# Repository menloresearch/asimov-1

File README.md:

# Asimov 1: Open-Source Humanoid Robot

Asimov is an open-source humanoid robot that you can build, train and customize.

<p align="center">
  <a href="https://asimov.inc">Website</a> ·
  <a href="https://manual.asimov.inc">Manual</a> ·
  <a href="https://asimov.inc/diy-kit">DIY Kit</a> ·
  <a href="https://static.asimov.inc/asimov/v1/asimov-v1-20260420.html">3D Model</a> ·
  <a href="https://discord.gg/HzDfGN7kUw">Discord</a> ·
  <a href="https://x.com/asimovinc">X</a> ·
  <a href="https://forum.menlo.ai">Forum</a>
</p>

Asimov 1 is a 1.2 m, 35 kg biped with 25 actuated degrees of freedom. This repository contains the mechanical CAD, electrical CAD, simulation model, and onboard software to build, simulate, and customize Asimov 1.

---

## Specifications

| Spec | Value |
|---|---|
| Height | 1.2 m |
| Weight | 35 kg |
| Degrees of Freedom | 25 actuated |
| Legs | 6 DOF x 2 |
| Arms | 5 DOF x 2 (shoulder pitch/roll/yaw, elbow, wrist yaw) |
| Torso | 1 DOF waist yaw, 10 W 4 ohm speaker, 6 DOF IMU |
| Head | 2 DOF neck (neck yaw, neck pitch), stereo microphone array, 2MP monocular camera |
| CAN Bus | 5 @ 1Mbps + 1 @ 500kbps |
| Onboard Compute | Raspberry Pi 5 (media + network) + Radxa CM5 (motion control) |
| Structural Materials | 7075 aluminium, MJF PA12 nylon |

| Activity | Rated Load | Peak Load |
|---|---|---|
| Squat | 5 kg | - |
| Bicep curl | 5 kg each arm | 15 kg each arm |
| Front raise | 5 kg each arm | 15 kg each arm |
| Lateral raise | 6 kg each arm | 18 kg each arm |

---

## Build your own Asimov

> [!TIP]
> **Option 1: DIY Kit:** Everything you need to build Asimov 1, unassembled. Shipping now for $20,000. [Order now →](https://menlo.ai/asimov-1#buy)

> [!NOTE]
> **Option 2: Self-source:** Pull the [BOM](https://docs.menlo.ai/asimov/1/assembly-preparations/self-source/select-release-and-bom) and fabricate everything yourself. [Assembly Manual →](https://docs.menlo.ai/asimov/1)

### DIY Kit

| Category | Included | Not Included |
|---|---|---|
| Hardware | All BOM components (unassembled), power supply & cabling, spare parts | Tools, hands |
| Compute | RPi edge board, motion control board, network board, power distribution board | 4G/5G modules |
| Sensors | Monocular camera, IMUs, mic, speaker, motor joint states | Lidar, 360 cam |
| Docs | Quick start guide, manual, DIY build videos | — |

**[Pre-order the Asimov 1 DIY Kit →](https://asimov.inc/diy-kit)**

### Self-source

Start with the repo-local [fabrication manifest](mechanical/FABRICATION_MANIFEST.csv) for the CAD-derived part inventory, then cross-reference the [BOM](https://manual.asimov.inc/v1/bom) and assembly manual for procurement details, sourcing, and fabrication notes.

The [shoe accessory](mechanical/accessories/shoes/README.md) is supplied as a single `ASV1_Shoes.STL`. The shoes are symmetric and the same geometry fits either foot: print two identical copies in TPU 95A using FDM, one per foot.

The [dummy hands](mechanical/accessories/dummy_hands/README.md) are supplied as `ASV1_DUMMY_HANDS.3mf`, a Bambu Studio project with embedded printing settings. See the [mechanical fabrication guide](mechanical/README.md) for the part-naming chart and material/process classes, and the [stool accessory](mechanical/accessories/stool/README.md) for its CAD, BOM, and fabrication specifications.

**[Assembly Manual →](https://manual.asimov.inc)**

---

## Fabrication manifest

The fabrication manifest inventories STEP and STL files under `mechanical/ASV1/*/FABRICATION`. Accessories have their own documentation under `mechanical/accessories`. Regenerate the manifest after changing the robot fabrication files, then verify it:

```bash
python3 scripts/generate_fabrication_manifest.py
python3 scripts/generate_fabrication_manifest.py --check
```

---

## Roadmap

| Status | Item |
|---|---|
| ✅ | Mechanical CAD — 7 subassemblies |
| ✅ | MuJoCo simulation model |
| ✅ | Electrical wiring harness |
| ✅ | Electrical schematics & PCB files |
| 🔜 | Asimov Edge |
| 🔜 | Locomotion policy |

---

## Work with us

- **Build questions?**: Ask in the [forum](https://forum.menlo.ai) or open a [GitHub Issue](https://github.com/asimovinc/asimov-v1/issues) for bugs and contributions.
- **Deploying Asimov?**: [Talk to us →](mailto:bd@menlo.ai)
- **Supply chain partner?**: If you manufacture actuators, structural components, or electronics and want to be part of the Asimov supply chain, reach out.
[bd@menlo.ai](mailto:bd@menlo.ai)

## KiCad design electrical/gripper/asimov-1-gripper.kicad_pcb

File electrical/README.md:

## Robot Processing Unit 
### Motion Control Board
- The Motion Control Board (MCB) is a carrier board designed for the Radxa CM5. It has an onboard IMU and contains the necessary motor communication buses for the robot to function.
- The Power Distribution Board (PDB) sits on top of the Motion Control Board (MCB) to form the 2 board stackup.

General information:
- Power is supplied via the XT90(2+2) connector on the PDB, with 5V being routed to the MCB at the bottom
- The UART TTL debug lines have been fanned out as test pads on the PDB for debugging purposes.
- The LSM6DSV IMU is located at the bottom of the MCB
- LCSC component IDs are attached in the KiCad source files for direct JLCPCB fabrication and assembly.

### Communication Ports

| Port Type | Quantity | Details |
|-----------|----------|---------|
| CAN (SPI-CAN) | 6 | CAN via SPI bridge |
| USB 2.0 | 2 | USB interfaces |
| Ethernet | 1 | 1Gbps |
| I2C | 1 | I2C interface |

### Port Mapping

| Port ID | Purpose |
|---------|---------|
| LL | Left leg bus |
| RL | Right leg bus |
| LA | Left arm bus |
| RA | Right arm bus |
| NP | Neck pitch connection for the torso bus |
| NY | Neck yaw connection for the torso bus |
| W  | Waist yaw connection for the torso bus |

> Please refer to the KiCAD source files for a detailed view of all pin mappings on the PDB

## Media Unit

The head of the robot contains a RPI5, with 2 boards to support its function.

Head board:
- contains buck converters to power the RPI5 with 5V
- an audio IC to handle the stereo microphones and stereo speakers, although only 1 speaker output is currently used

RPI5 Hat:
- a small hat that allows for a clean 5V connection to the headers of the RPI5
- contains a button, LED and buzzer for basic status messages, similar to a consumer motherboard

## Wiring

- Each line refers to a pre-made cable on the robot
- Certain connections can only be complete post assembly due to space contraints. These connections have been marked with the Joint names WAGO or SOLDER.

> If making cables from scratch, double-check wire pathing to make sure there is sufficient slack on each connection.

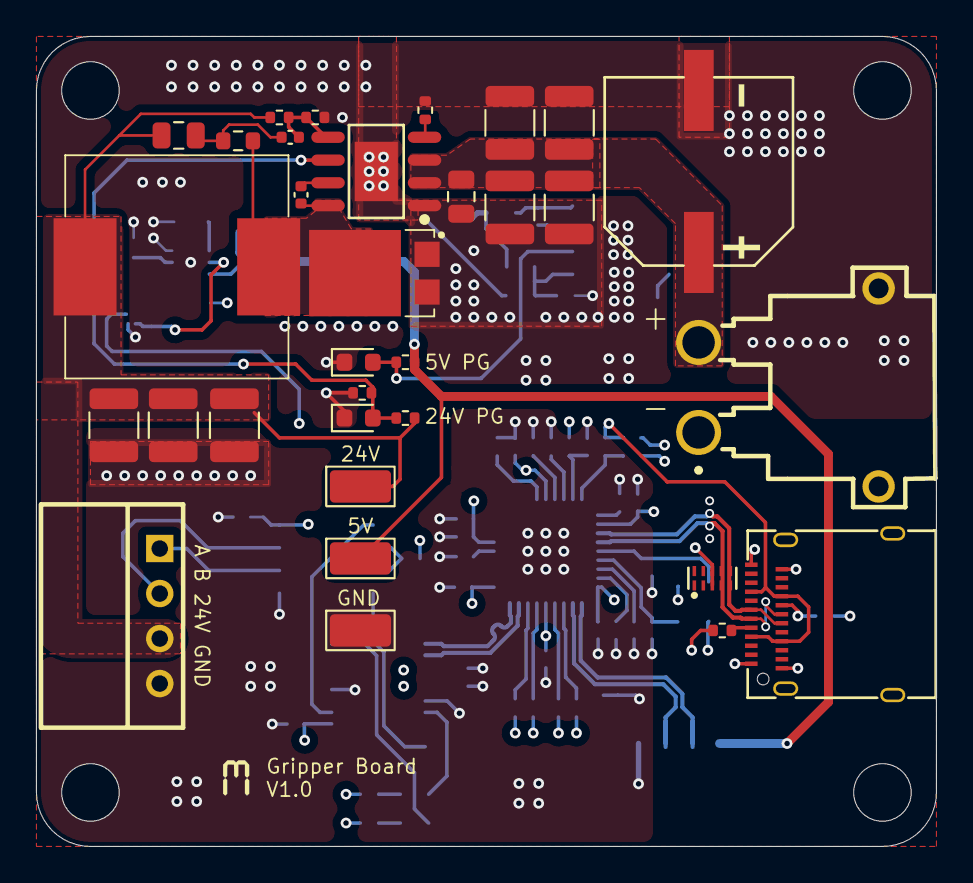
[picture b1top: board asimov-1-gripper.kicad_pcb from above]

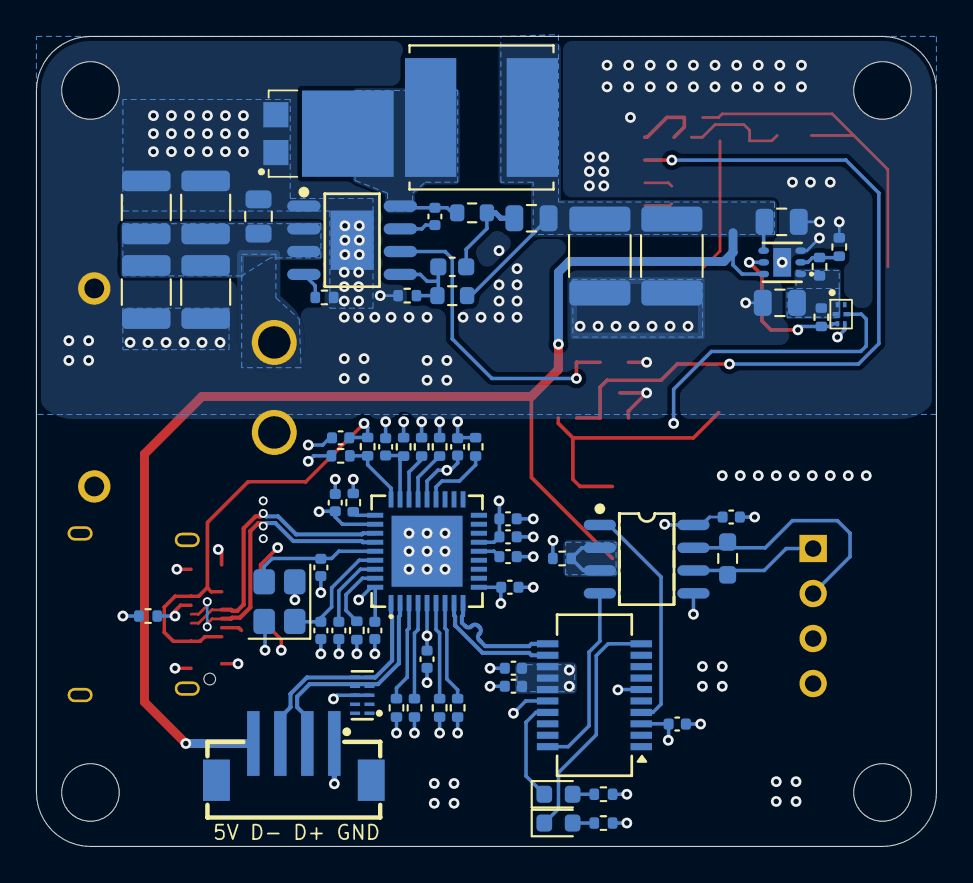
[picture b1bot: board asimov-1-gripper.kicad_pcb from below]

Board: 4 copper layers, 50.0 x 45.0 mm, 102 parts (66 on the bottom side), 53 nets.

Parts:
C101: 100V, 33u; CAP-SMD_BD10.0-L10.3-W10.3-FD
C201, C202, C203, C204, C209, C210, C211, C301, C302, C303, C304: 100V, 10u; C_1210_3225Metric
C205, C305: 100V, 100n; C_0805_2012Metric
C206, C306: 2.2n; C_0402_1005Metric
C207: 47p; C_0402_1005Metric
C208, C308: 3.3n; C_0805_2012Metric
C307: 180p; C_0603_1608Metric
C309, C310: 22u; C_1812_4532Metric
C401, C402: 1u; C_0805_2012Metric
C501, C502, C503, C504, C507, C508, C509, C510, C511, C512, C513, C601, C602, C603, C604: 100n; C_0402_1005Metric
C505, C506: 18p; C_0402_1005Metric
D101, D102: PUSB3FR4Z; DFN2510-10_L2.5-W1.0-P0.50-BL-2
D201, D301, D601, D602: LED_Red; LED_0603_1608Metric
D202, D302: V8P12-M3/86A; TO-277A_L6.1-W4.3-LS6.5-BR
H101, H102, H103, H104: MountingHole; MountingHole_3.2mm_M3
J101: Conn_01x04; CONN-TH_XT30PW-M
J102: USB_C_Receptacle; USB-C-SMD_TYPE-C-24P
J103: Camera USB; CONN-SMD_4P-P1.50_B4B-ZR-SM4-TF
J104: Servo Connection; CONN-TH_22057045
L201: 68u; IND-SMD_L12.0-W12.0_744771008
L301: 47u; IND_SRN8040TA-470M
R101, R102: 5.1k; R_0402_1005Metric
R201: 200k; R_0402_1005Metric
R202, R206, R305: 49.9k; R_0402_1005Metric
R203, R302, R509, R510, R511, R512, R601, R602, R603: 10k; R_0402_1005Metric
R204: 402k; R_0603_1608Metric
R205: 953k; R_0402_1005Metric
R301: 41.2k; R_0402_1005Metric
R303: 180k; R_0603_1608Metric
R304: 158k; R_0603_1608Metric
R401, R403, R501, R502, R503, R504, R505, R506, R507: 100k; R_0402_1005Metric
R402: 20k; R_0402_1005Metric
R508: 12k; R_0402_1005Metric
R604: 120; R_0603_1608Metric_Pad0.98x0.95mm_HandSolder
TP101: GND Test Point; TestPoint_Keystone_5015_Micro_Mini
TP102: 5V Test Point; TestPoint_Keystone_5015_Micro_Mini
TP103: 24V Test Point; TestPoint_Keystone_5015_Micro_Mini
U201, U301: LM5013DDAR; ESOP-8_L4.9-W3.9-P1.27-LS6.0-BL-EP-1
U401: TPS74501PDRVR; WSON-6_L2.0-W2.0-P0.65-TL-EP
U402: TPS22995; DFN-6_L1.3-W0.9_TPS22995RZFR
U501: USB2514BT-I/M2; QFN-36_L6.0-W6.0-P0.50-BL-EP
U601: FT231XS; SSOP-20_3.9x8.7mm_P0.635mm
U602: THVD1406; SOIC-8_L4.9-W3.9-P1.27-LS6.0-BL
Y501: 24MHz 12pF; Crystal_SMD_3225-4Pin_3.2x2.5mm

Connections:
+3V3: C507.1, C508.1, C509.1, C510.1, C511.1, C512.1, C513.1, C601.1, C602.1, C603.1, C604.1, R501.1, R509.1, R510.1, R511.1, R512.1, R601.1, R602.1, R603.2, U402.5 (VOUT), U501.5 (VDDA33), U501.10 (VDDA33), U501.15 (VDD33), U501.23 (VDD33), U501.29 (VDDA33), U501.36 (VDDA33), U601.3 (VCCIO), U601.13 (3V3OUT), U601.14 (~RESET), U601.15 (VCC), U602.8 (VCC)
+5V: C308.2, C309.1, C310.1, C401.1, J103.4, L301.2, R302.1, R304.1, TP102.1 (1_1), U401.4 (EN), U401.6 (IN)
+24V: C208.2, C209.1, C210.1, C211.1, J104.3, L201.2, R202.1, R205.1, TP103.1 (1_1)
+BATT: C101.1, C201.1, C202.1, C203.1, C204.1, C205.1, C301.1, C302.1, C303.1, C304.1, C305.1, J101.2, U201.2 (VIN), U201.3 (EN/UVLO), U301.2 (VIN), U301.3 (EN/UVLO)
/USB2Hub/DFP1_D+: D102.4 (CH3), D102.7 (CH3), J103.2, U501.2 (USBDP_DN1/PRT_DIS_P1)
/USB2Hub/DFP1_D-: D102.5 (CH4), D102.6 (CH4), J103.3, U501.1 (USBDM_DN1/PRT_DIS_M1)
/USB2Hub/DFP4_D+: U501.9 (USBDP_DN4/PRT_DIS_P4), U601.11 (USBDP)
/USB2Hub/DFP4_D-: U501.8 (USBDM_DN4/PRT_DIS_M4), U601.12 (USBDM)
/USB2Hub/UFP_D+: D101.4 (CH3), D101.7 (CH3), J102.A6 (D+), J102.B6 (D+), U501.31 (USBDP_UP)
/USB2Hub/UFP_D-: D101.5 (CH4), D101.6 (CH4), J102.A7 (D-), J102.B7 (D-), U501.30 (USBDM_UP)
/USBToRS485/RS485_A: J104.1, R604.2, U602.6 (A)
/USBToRS485/RS485_B: J104.2, R604.1, U602.7 (B)
/USBToRS485/RX_3V3: U601.4 (RXD), U602.1 (R)
/USBToRS485/TX_3V3: U601.20 (TXD), U602.4 (D)
GND: C101.2, C201.2, C202.2, C203.2, C204.2, C205.2, C209.2, C210.2, C211.2, C301.2, C302.2, C303.2, C304.2, C305.2, C309.2, C310.2, C401.2, C402.2, C501.2, C502.2, C503.2, C504.2, C505.1, C506.1, C507.2, C508.2, C509.2, C510.2, C511.2, C512.2, C513.2, C601.2, C602.2, C603.2, C604.2, D101.3 (GND), D101.8 (GND), D102.3 (GND), D102.8 (GND), D201.1 (K), D202.1 (A), D202.2 (A), D301.1 (K), D302.1 (A), D302.2 (A), J101.1, J101.3, J101.4, J102.A1 (GND), J102.A12 (GND), J102.B1 (GND), J102.B12 (GND), J103.1, J104.4, R101.2, R102.2, R201.2, R203.1, R206.2, R301.2, R305.2, R402.2, R503.2, R504.1, R505.1, R506.1, R507.1, R508.2, TP101.1 (1_1), U201.1 (GND), U201.9 (EP), U301.1 (GND), U301.9 (EP), U401.3 (GND), U401.7 (EP), U402.4 (GND), U501.37 (EP), U601.6 (GND), U601.16 (GND), U602.5 (GND), Y501.2 (G), Y501.4 (G)
unnamed: C207.1, C208.1, R204.2
unnamed: C307.1, C308.1, R303.2
unnamed: D201.2 (A), R202.2, R203.2, U201.6 (PGOOD)
unnamed: C206.2, D202.3 (K), L201.1, R204.1, U201.8 (SW)
unnamed: D301.2 (A), R302.2, U301.6 (PGOOD)
unnamed: C306.2, D302.3 (K), L301.1, R303.1, U301.8 (SW)
unnamed: D601.2 (A), R601.2
unnamed: D601.1 (K), U601.17 (CBUS1)
unnamed: D602.2 (A), R602.2
unnamed: D602.1 (K), U601.10 (CBUS2)
unnamed: J102.A5 (CC1), R101.1
unnamed: J102.B5 (CC2), R102.1
unnamed: C206.1, U201.7 (BST)
unnamed: C207.2, R205.2, R206.1, U201.5 (FB)
unnamed: R201.1, U201.4 (RON)
unnamed: C306.1, U301.7 (BST)
unnamed: C307.2, R304.2, R305.1, U301.5 (FB)
unnamed: R301.1, U301.4 (RON)
unnamed: R401.2, R402.1, U401.2 (FB)
unnamed: C402.1, R401.1, R403.1, U401.1 (OUT), U402.1 (VBIAS), U402.2 (VIN)
unnamed: R403.2, U401.5 (PG), U402.3 (ON)
unnamed: C502.1, U501.14 (CRFILT)
unnamed: R505.2, U501.25 (HS_IND/CFG_SEL1)
unnamed: C504.1, U501.34 (PLLFILT)
unnamed: R508.1, U501.35 (RBIAS)
unnamed: C501.1, R501.2, U501.26 (RESET_N)
unnamed: R504.2, U501.24 (SCL/SMBCLK/CFG_SEL0)
unnamed: R507.2, U501.22 (SDA/SMBBATA/NON_REM1)
unnamed: R506.2, U501.28 (SUSP_IND/LOCAL_PWR/NON_REM0)
unnamed: R509.2, U501.3 (USBDM_DN2/PRT_DIS_M2)
unnamed: R511.2, U501.6 (USBDM_DN3/PRT_DIS_M3)
unnamed: R510.2, U501.4 (USBDP_DN2/PRT_DIS_P2)
unnamed: R512.2, U501.7 (USBDP_DN3/PRT_DIS_P3)
unnamed: R502.2, R503.1, U501.27 (VBUS_DET)
unnamed: C505.2, U501.33 (XTALIN/CLKIN), Y501.1
unnamed: C506.2, U501.32 (XTALOUT), Y501.3
unnamed: R603.1, U602.2 (~RE), U602.3 (~SHDN)
VBUS: C503.1, J102.A4 (VBUS), J102.A9 (VBUS), J102.B4 (VBUS), J102.B9 (VBUS), R502.1

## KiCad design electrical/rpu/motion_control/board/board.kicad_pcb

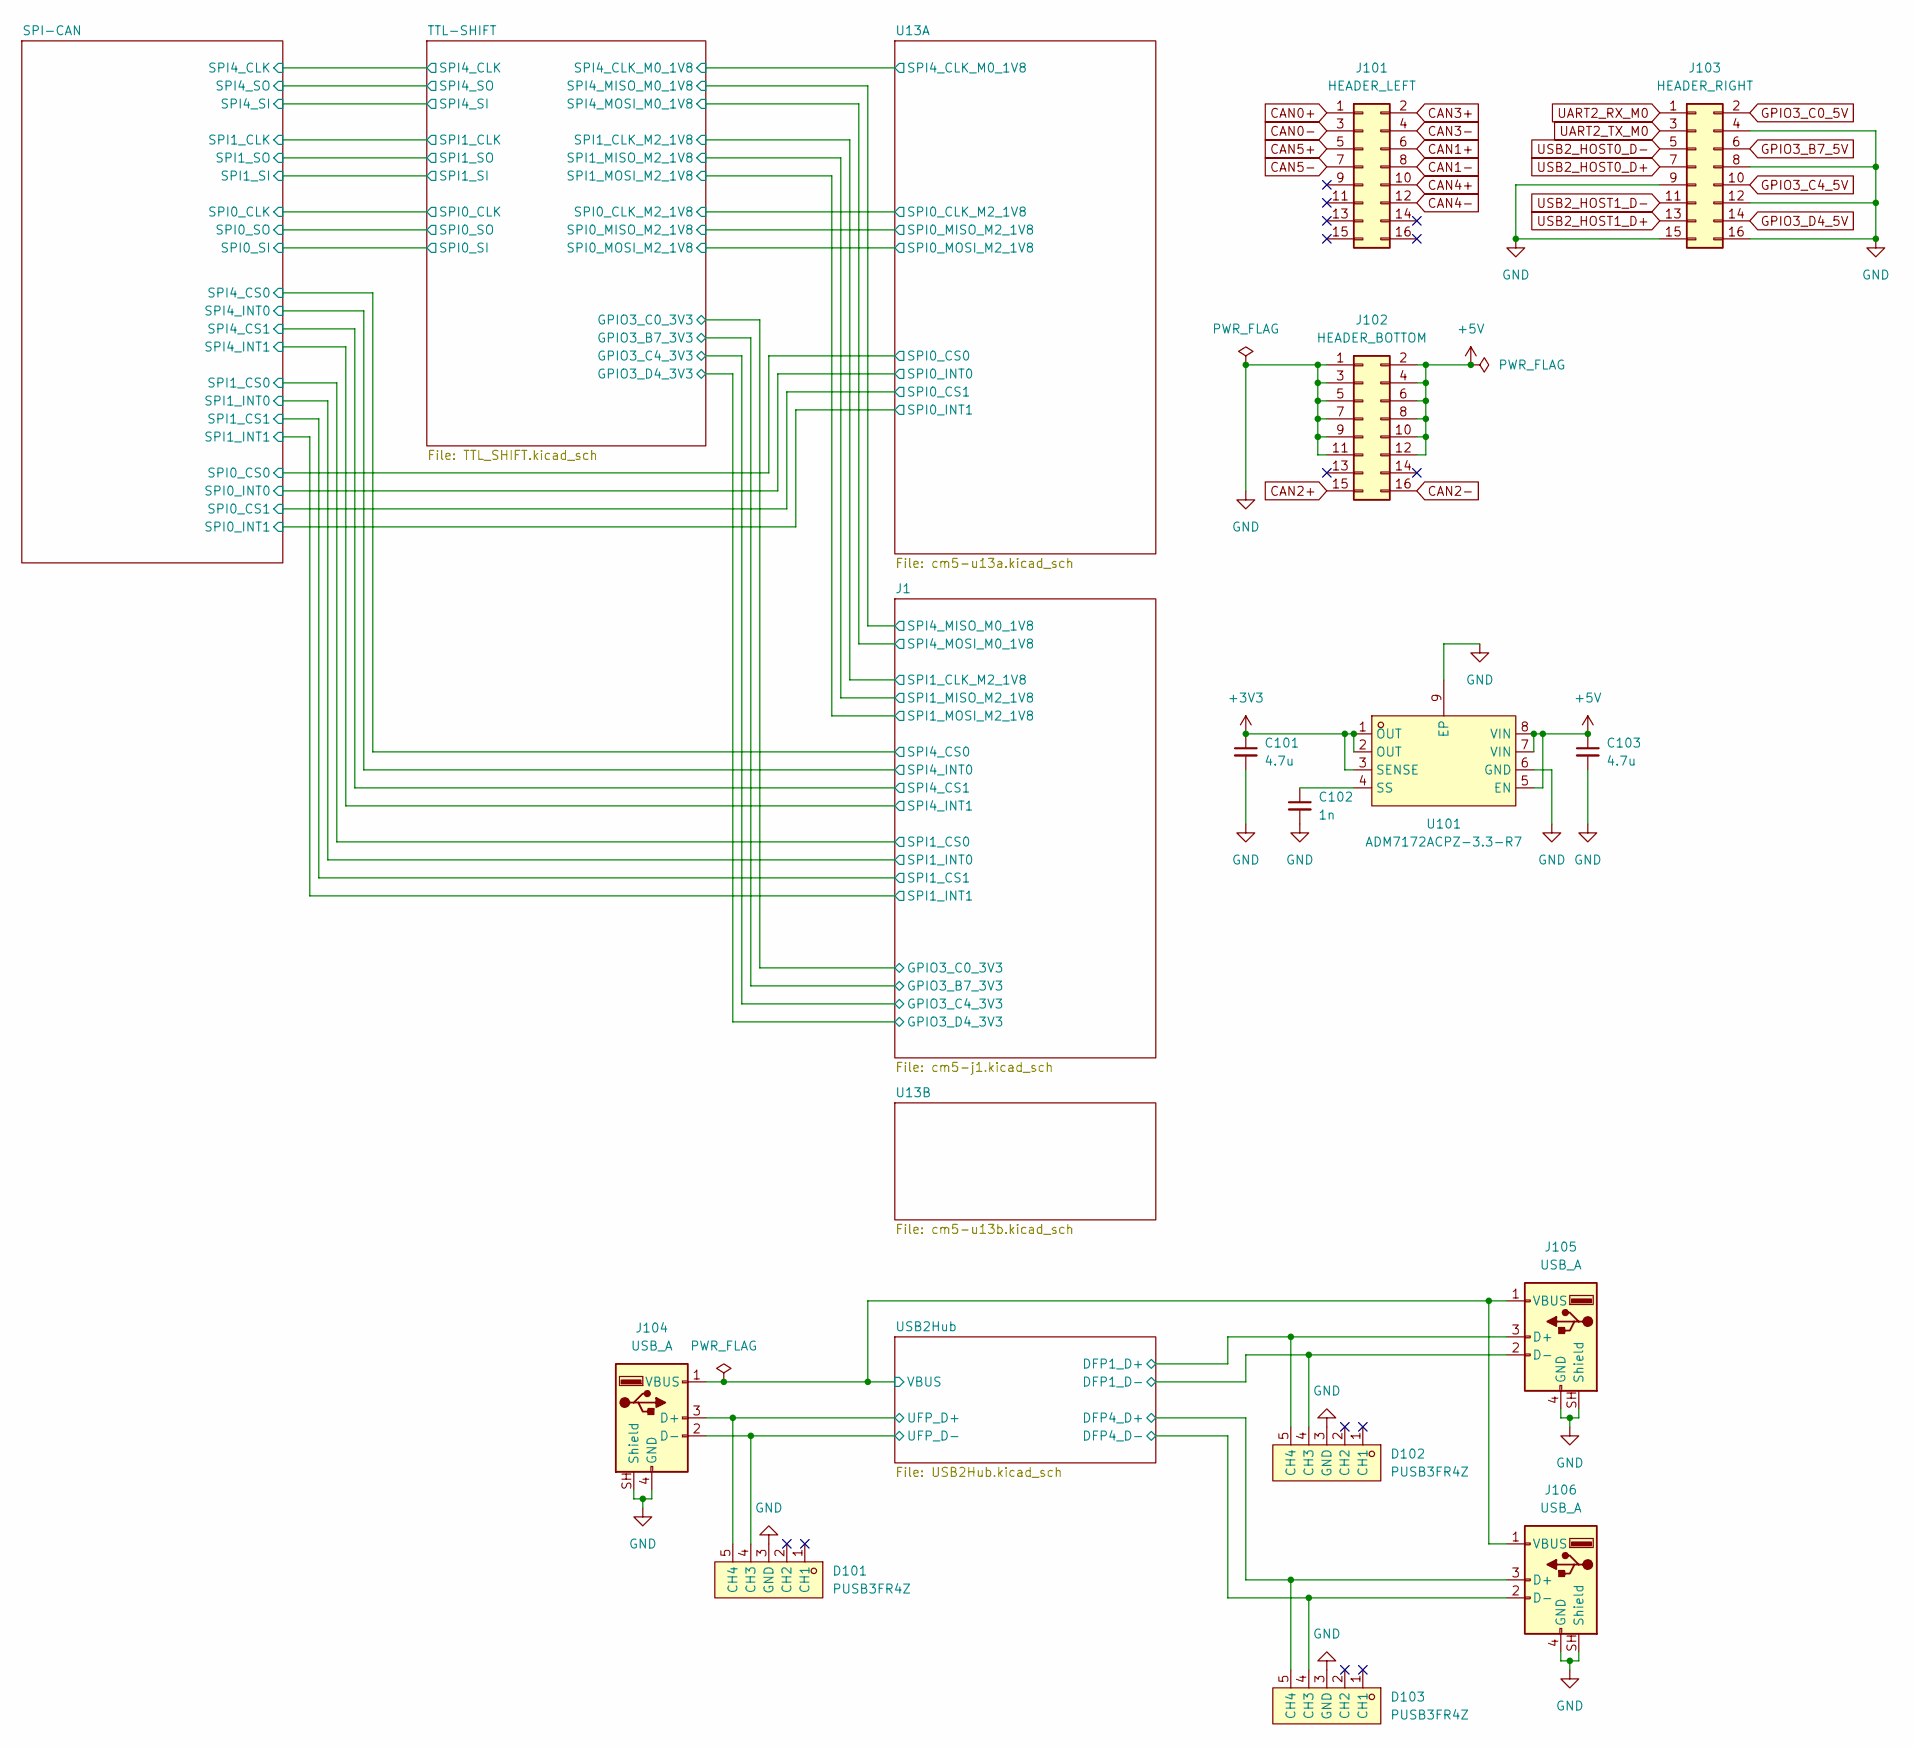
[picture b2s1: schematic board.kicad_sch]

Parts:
C101, C103: 4.7u; C_0402_1005Metric; LCSC C368809
C102: 1n; C_0402_1005Metric; LCSC C76947
D101, D102, D103: PUSB3FR4Z; DFN2510-10_L2.5-W1.0-P0.50-BL-2; MPN PUSB3FR4Z; LCSC Part C503418
J101: HEADER_LEFT; PinHeader_2x08_P2.54mm_Vertical; LCSC C492425
J102: HEADER_BOTTOM; PinHeader_2x08_P2.54mm_Vertical; LCSC C492425
J103: HEADER_RIGHT; PinHeader_2x08_P2.54mm_Vertical; LCSC C492425
J104, J105, J106: USB_A; USB-A-TH_FUS264-FDSW3K; LCSC C305910
U101: ADM7172ACPZ-3.3-R7; DFN-8_L3.0-W3.0-P0.50-BL-EP; MPN ADM7172ACPZ-3.3-R7; LCSC Part C514342

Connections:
+3V3: C101.1, U101.1 (OUT), U101.2 (OUT), U101.3 (SENSE); also elsewhere on the board
+5V: C103.1, J102.2, J102.4, J102.6, J102.8, J102.10, J102.12, U101.5 (EN), U101.7 (VIN), U101.8 (VIN); also elsewhere on the board
/USB2Hub/DFP1_D+: D102.5 (CH4), D102.6 (CH4), J105.3 (D+); also elsewhere on the board
/USB2Hub/DFP1_D-: D102.4 (CH3), D102.7 (CH3), J105.2 (D-); also elsewhere on the board
/USB2Hub/DFP4_D+: D103.5 (CH4), D103.6 (CH4), J106.3 (D+); also elsewhere on the board
/USB2Hub/DFP4_D-: D103.4 (CH3), D103.7 (CH3), J106.2 (D-); also elsewhere on the board
/USB2Hub/UFP_D+: D101.5 (CH4), D101.6 (CH4), J104.3 (D+); also elsewhere on the board
/USB2Hub/UFP_D-: D101.4 (CH3), D101.7 (CH3), J104.2 (D-); also elsewhere on the board
/USB2Hub/VBUS: J104.1 (VBUS), J105.1 (VBUS), J106.1 (VBUS); also elsewhere on the board
CAN0+: J101.1; also elsewhere on the board
CAN0-: J101.3; also elsewhere on the board
CAN1+: J101.6; also elsewhere on the board
CAN1-: J101.8; also elsewhere on the board
CAN2+: J102.15; also elsewhere on the board
CAN2-: J102.16; also elsewhere on the board
CAN3+: J101.2; also elsewhere on the board
CAN3-: J101.4; also elsewhere on the board
CAN4+: J101.10; also elsewhere on the board
CAN4-: J101.12; also elsewhere on the board
CAN5+: J101.5; also elsewhere on the board
CAN5-: J101.7; also elsewhere on the board
GND: C101.2, C102.2, C103.2, D101.3 (GND), D101.8 (GND), D102.3 (GND), D102.8 (GND), D103.3 (GND), D103.8 (GND), J102.1, J102.3, J102.5, J102.7, J102.9, J102.11, J103.4, J103.8, J103.9, J103.12, J103.15, J103.16, J104.4 (GND), J104.SH (Shield), J105.4 (GND), J105.SH (Shield), J106.4 (GND), J106.SH (Shield), U101.6 (GND), U101.9 (EP); also elsewhere on the board
GPIO3_B7_5V: J103.6; also elsewhere on the board
GPIO3_C0_5V: J103.2; also elsewhere on the board
GPIO3_C4_5V: J103.10; also elsewhere on the board
GPIO3_D4_5V: J103.14; also elsewhere on the board
unnamed: C102.1, U101.4 (SS)
UART2_RX_M0: J103.1; also elsewhere on the board
UART2_TX_M0: J103.3; also elsewhere on the board
USB2_HOST0_D+: J103.7; also elsewhere on the board
USB2_HOST0_D-: J103.5; also elsewhere on the board
USB2_HOST1_D+: J103.13; also elsewhere on the board
USB2_HOST1_D-: J103.11; also elsewhere on the board

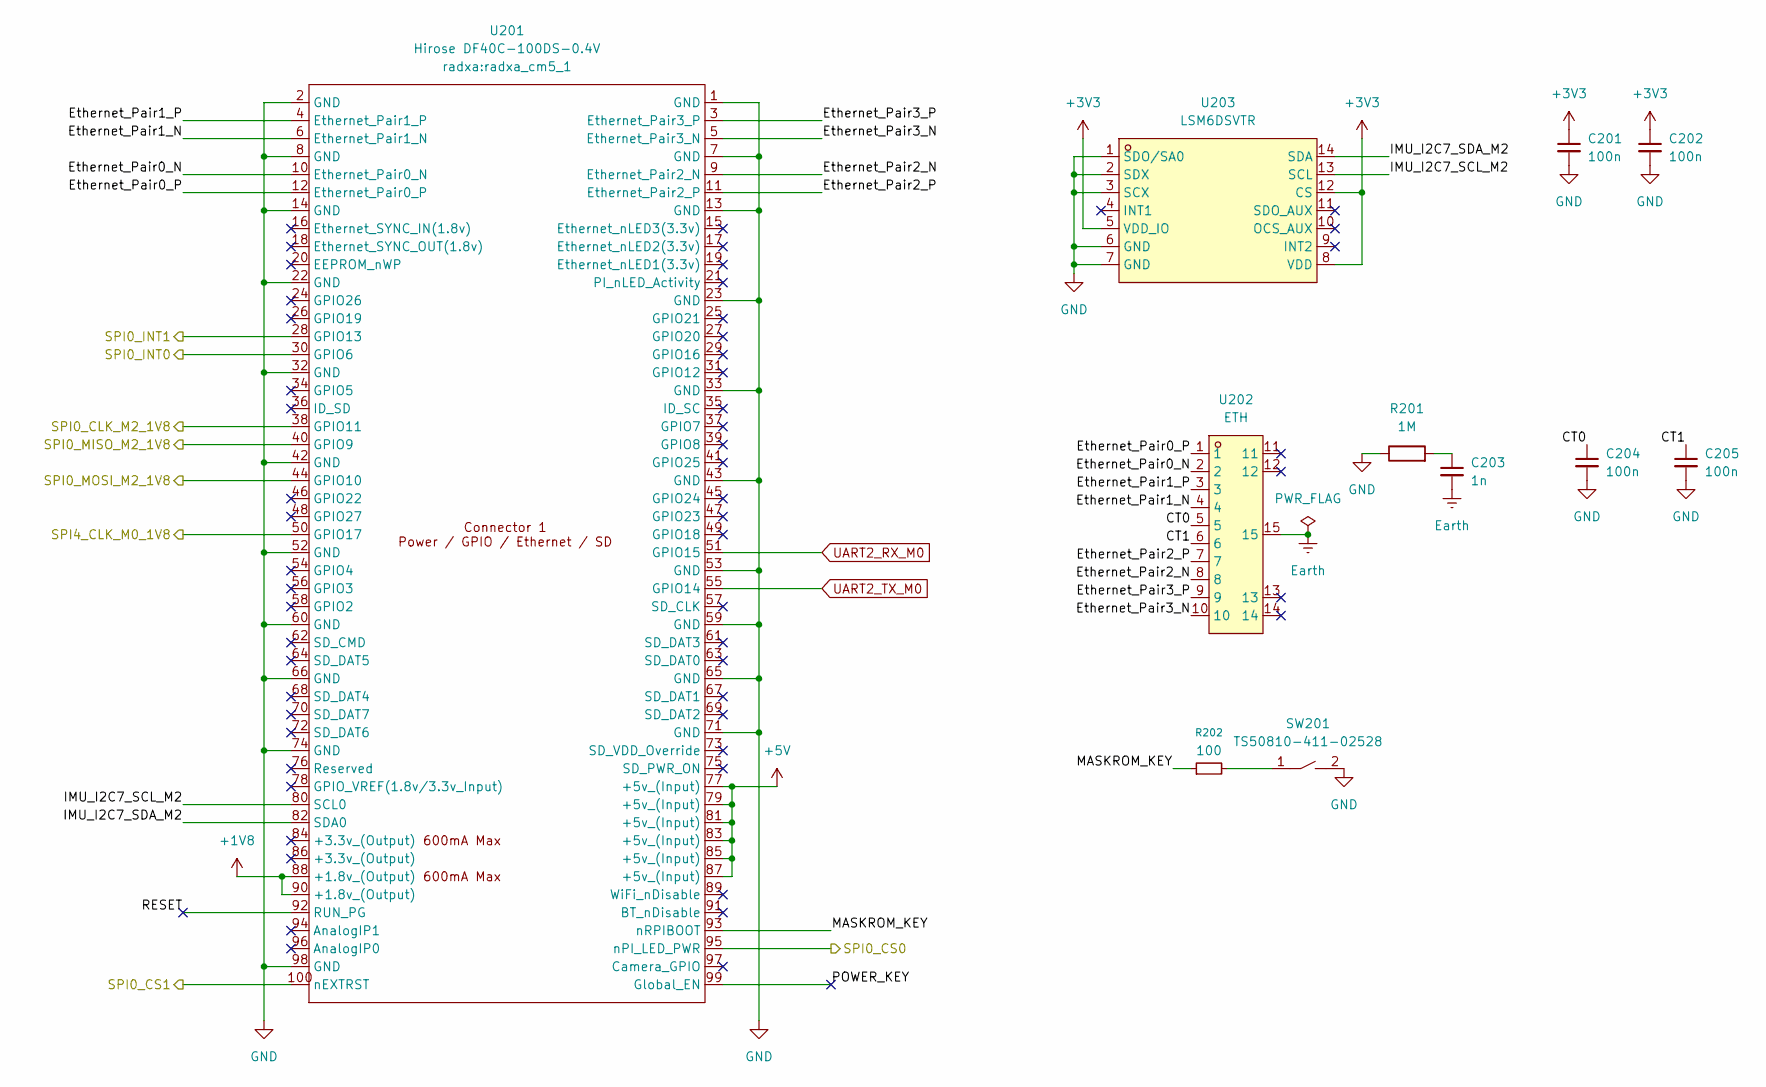
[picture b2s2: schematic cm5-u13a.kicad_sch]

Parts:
C201, C202: 100n; C_0402_1005Metric; LCSC C77020
C203: 1n; C_1206_3216Metric; LCSC C23631
C204, C205: 100n; C_0402_1005Metric; LCSC C541464
R201: 1M; R_2010_5025Metric; LCSC C1513439
R202: 100; R_0402_1005Metric; LCSC C106232
SW201: TS50810-411-02528; SW-SMD_L6.2-W3.7-LS8.0; MPN TS50810-411-02528; LCSC Part C42400876
U201: Hirose DF40C-100DS-0.4V; radxa_cm5_1; LCSC C597931
U202: ETH; RJ45-SMD_HR963380AE; MPN HR963380AE; LCSC Part C19724763
U203: LSM6DSVTR; LGA-14_L3.0-W2.5-P0.50-TL; LCSC Part C5267399

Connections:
+1V8: U201.88 (+1.8v_(Output)), U201.90 (+1.8v_(Output)); also elsewhere on the board
+3V3: C201.1, C202.1, U203.5 (VDD_IO), U203.8 (VDD), U203.12 (CS); also elsewhere on the board
+5V: U201.77 (+5v_(Input)), U201.79 (+5v_(Input)), U201.81 (+5v_(Input)), U201.83 (+5v_(Input)), U201.85 (+5v_(Input)), U201.87 (+5v_(Input)); also elsewhere on the board
/SPI-CAN/SPI0_CS0: U201.95 (nPI_LED_PWR); also elsewhere on the board
/SPI-CAN/SPI0_CS1: U201.100 (nEXTRST); also elsewhere on the board
/SPI-CAN/SPI0_INT0: U201.30 (GPIO6); also elsewhere on the board
/SPI-CAN/SPI0_INT1: U201.28 (GPIO13); also elsewhere on the board
/TTL-SHIFT/SPI0_CLK_M2_1V8: U201.38 (GPIO11); also elsewhere on the board
/TTL-SHIFT/SPI0_MISO_M2_1V8: U201.40 (GPIO9); also elsewhere on the board
/TTL-SHIFT/SPI0_MOSI_M2_1V8: U201.44 (GPIO10); also elsewhere on the board
/TTL-SHIFT/SPI4_CLK_M0_1V8: U201.50 (GPIO17); also elsewhere on the board
/U13A/CT0: C204.1, U202.5
/U13A/CT1: C205.1, U202.6
/U13A/Ethernet_Pair0_N: U201.10 (Ethernet_Pair0_N), U202.2
/U13A/Ethernet_Pair0_P: U201.12 (Ethernet_Pair0_P), U202.1
/U13A/Ethernet_Pair1_N: U201.6 (Ethernet_Pair1_N), U202.4
/U13A/Ethernet_Pair1_P: U201.4 (Ethernet_Pair1_P), U202.3
/U13A/Ethernet_Pair2_N: U201.9 (Ethernet_Pair2_N), U202.8
/U13A/Ethernet_Pair2_P: U201.11 (Ethernet_Pair2_P), U202.7
/U13A/Ethernet_Pair3_N: U201.5 (Ethernet_Pair3_N), U202.10
/U13A/Ethernet_Pair3_P: U201.3 (Ethernet_Pair3_P), U202.9
/U13A/IMU_I2C7_SCL_M2: U201.80 (SCL0), U203.13 (SCL)
/U13A/IMU_I2C7_SDA_M2: U201.82 (SDA0), U203.14 (SDA)
/U13A/MASKROM_KEY: R202.1, U201.93 (nRPIBOOT)
/U13A/POWER_KEY: U201.99 (Global_EN)
/U13A/RESET: U201.92 (RUN_PG)
Earth: C203.2, U202.15
GND: C201.2, C202.2, C204.2, C205.2, R201.1, SW201.2, U201.1 (GND), U201.2 (GND), U201.7 (GND), U201.8 (GND), U201.13 (GND), U201.14 (GND), U201.22 (GND), U201.23 (GND), U201.32 (GND), U201.33 (GND), U201.42 (GND), U201.43 (GND), U201.52 (GND), U201.53 (GND), U201.59 (GND), U201.60 (GND), U201.65 (GND), U201.66 (GND), U201.71 (GND), U201.74 (GND), U201.98 (GND), U203.1 (SDO/SA0), U203.2 (SDX), U203.3 (SCX), U203.6 (GND), U203.7 (GND); also elsewhere on the board
unnamed: C203.1, R201.2
unnamed: R202.2, SW201.1
UART2_RX_M0: U201.51 (GPIO15); also elsewhere on the board
UART2_TX_M0: U201.55 (GPIO14); also elsewhere on the board

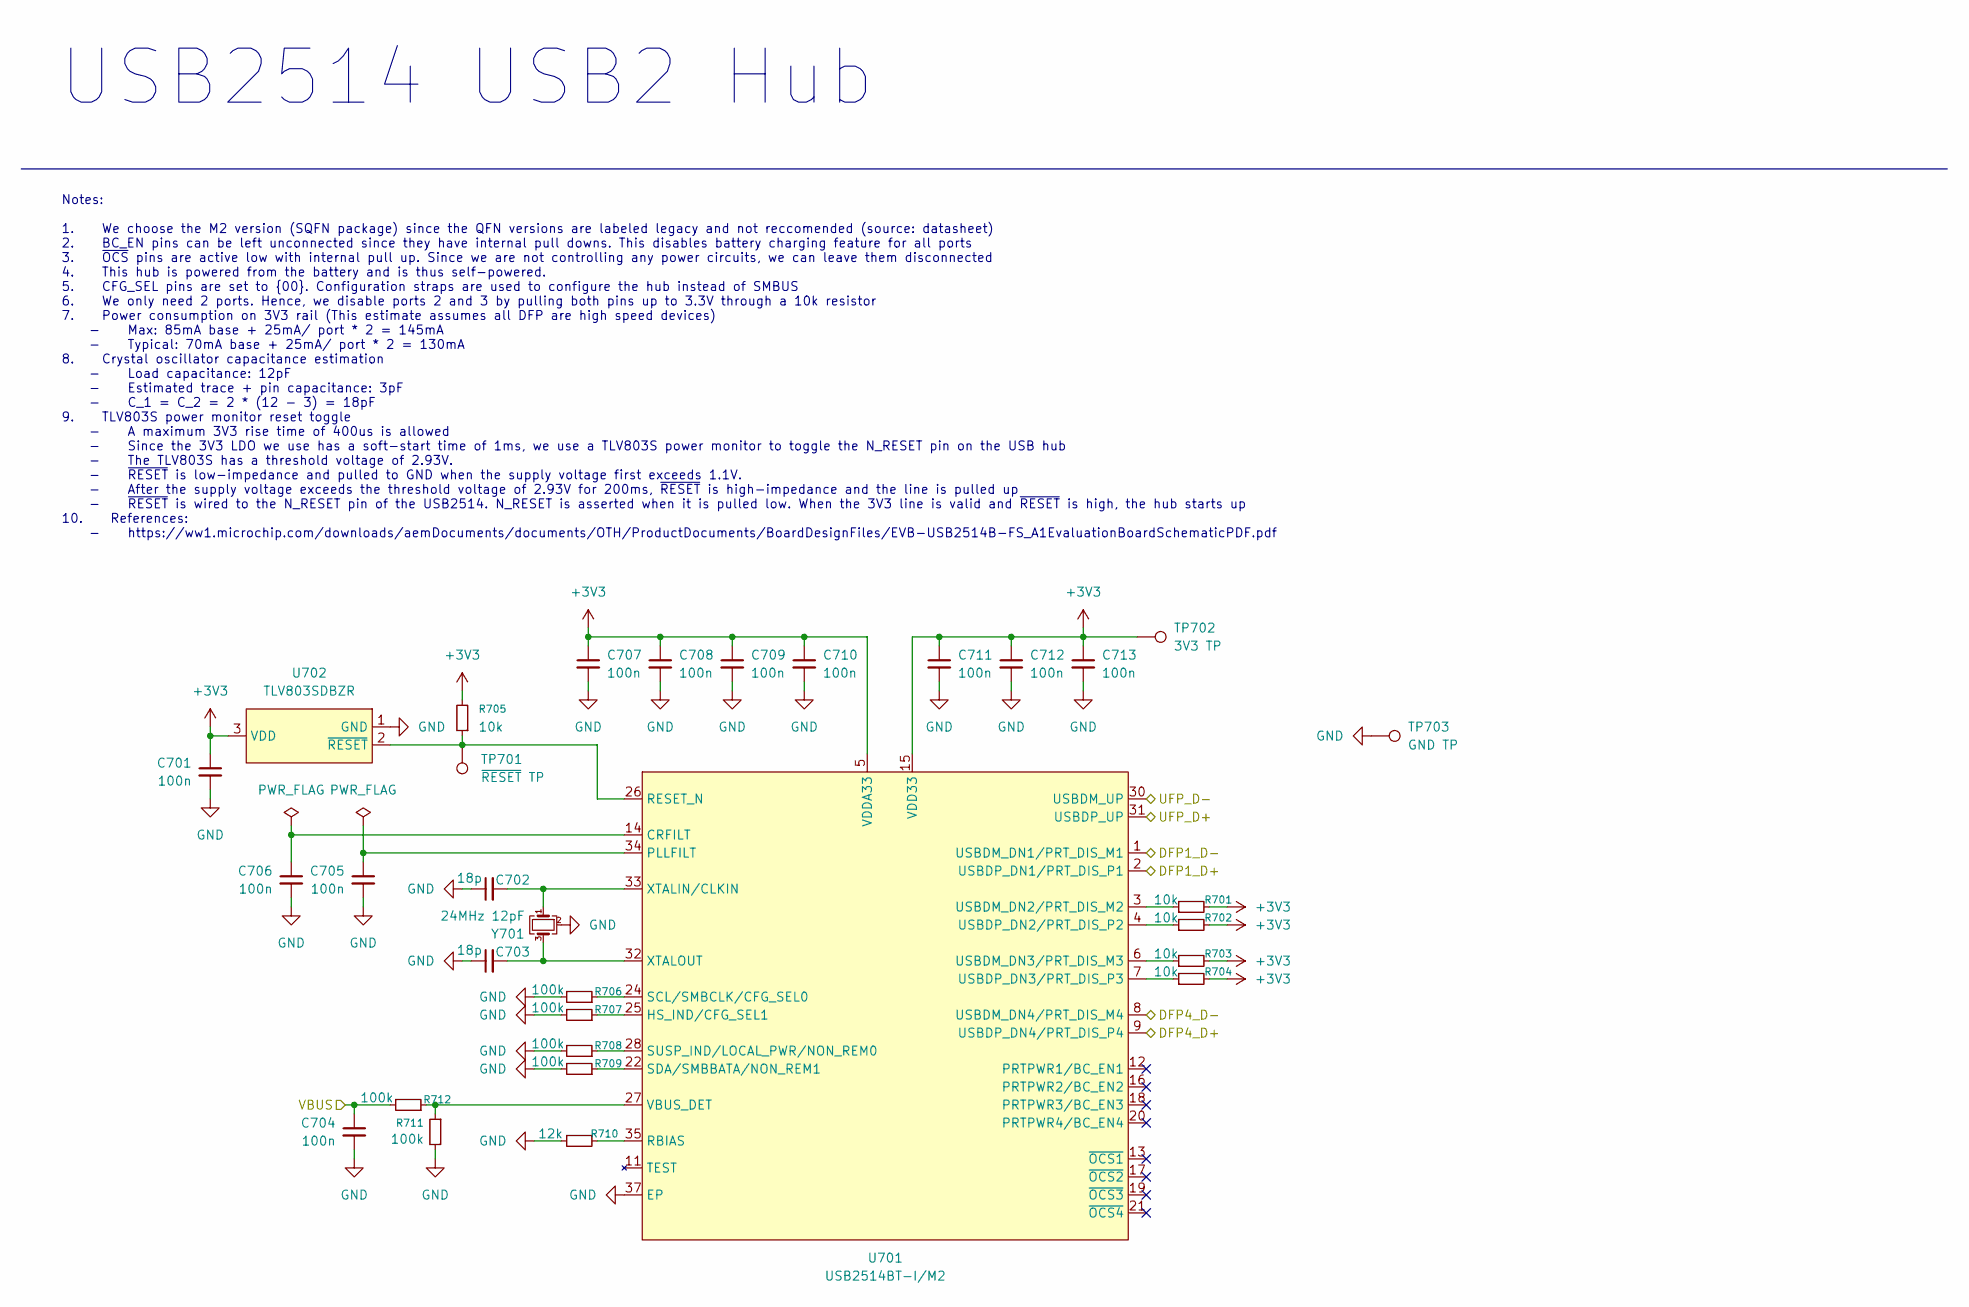
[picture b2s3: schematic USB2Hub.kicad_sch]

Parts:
C701, C704, C705, C706, C707, C708, C709, C710, C711, C712, C713: 100n; C_0402_1005Metric; LCSC C77020
C702, C703: 18p; C_0402_1005Metric; LCSC C1549
R701, R702, R703, R704, R705: 10k; R_0402_1005Metric; LCSC C190095
R706, R707, R708, R709, R711, R712: 100k; R_0402_1005Metric; LCSC C25741
R710: 12k; R_0402_1005Metric; LCSC C25752
TP701: ~{RESET} TP; TestPoint_Keystone_5015_Micro_Mini; LCSC C5199798
TP702: 3V3 TP; TestPoint_Keystone_5015_Micro_Mini; LCSC C5199798
TP703: GND TP; TestPoint_Keystone_5015_Micro_Mini; LCSC C5199798
U701: USB2514BT-I/M2; QFN-36_L6.0-W6.0-P0.50-BL-EP; MPN USB2514BT-I/M2; LCSC Part C510949
U702: TLV803SDBZR; SOT-23-3_L2.9-W1.3-P1.90-LS2.4-BR; MPN TLV803SDBZR; LCSC Part C132016
Y701: 24MHz 12pF; Crystal_SMD_3225-4Pin_3.2x2.5mm; LCSC C255917

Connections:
+3V3: C701.1, C707.1, C708.1, C709.1, C710.1, C711.1, C712.1, C713.1, R701.2, R702.2, R703.2, R704.2, R705.2, TP702.1 (1_1), U701.5 (VDDA33), U701.10 (VDDA33), U701.15 (VDD33), U701.23 (VDD33), U701.29 (VDDA33), U701.36 (VDDA33), U702.3 (VDD); also elsewhere on the board
/USB2Hub/DFP1_D+: U701.2 (USBDP_DN1/PRT_DIS_P1); also elsewhere on the board
/USB2Hub/DFP1_D-: U701.1 (USBDM_DN1/PRT_DIS_M1); also elsewhere on the board
/USB2Hub/DFP4_D+: U701.9 (USBDP_DN4/PRT_DIS_P4); also elsewhere on the board
/USB2Hub/DFP4_D-: U701.8 (USBDM_DN4/PRT_DIS_M4); also elsewhere on the board
/USB2Hub/UFP_D+: U701.31 (USBDP_UP); also elsewhere on the board
/USB2Hub/UFP_D-: U701.30 (USBDM_UP); also elsewhere on the board
/USB2Hub/VBUS: C704.1, R712.2; also elsewhere on the board
GND: C701.2, C702.1, C703.1, C704.2, C705.2, C706.2, C707.2, C708.2, C709.2, C710.2, C711.2, C712.2, C713.2, R706.2, R707.2, R708.2, R709.2, R710.2, R711.2, TP703.1 (1_1), U701.37 (EP), U702.1 (GND), Y701.2 (G), Y701.4 (G); also elsewhere on the board
unnamed: C706.1, U701.14 (CRFILT)
unnamed: R707.1, U701.25 (HS_IND/CFG_SEL1)
unnamed: C705.1, U701.34 (PLLFILT)
unnamed: R710.1, U701.35 (RBIAS)
unnamed: R705.1, TP701.1 (1_1), U701.26 (RESET_N), U702.2 (~RESET)
unnamed: R706.1, U701.24 (SCL/SMBCLK/CFG_SEL0)
unnamed: R709.1, U701.22 (SDA/SMBBATA/NON_REM1)
unnamed: R708.1, U701.28 (SUSP_IND/LOCAL_PWR/NON_REM0)
unnamed: R701.1, U701.3 (USBDM_DN2/PRT_DIS_M2)
unnamed: R703.1, U701.6 (USBDM_DN3/PRT_DIS_M3)
unnamed: R702.1, U701.4 (USBDP_DN2/PRT_DIS_P2)
unnamed: R704.1, U701.7 (USBDP_DN3/PRT_DIS_P3)
unnamed: R711.1, R712.1, U701.27 (VBUS_DET)
unnamed: C702.2, U701.33 (XTALIN/CLKIN), Y701.1
unnamed: C703.2, U701.32 (XTALOUT), Y701.3

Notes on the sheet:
USB2514 USB2 Hub
Notes: 1. We choose the M2 version (SQFN package) since the QFN versions are labeled legacy and not reccomended (source: datasheet) 2. BC_EN pins can be left unconnected since they have internal pull downs. This disables battery charging feature for all ports 3. ~{OCS} pins are active low with inte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

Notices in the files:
README.md:
License: CERN-OHL-S-2.0
License: Software
